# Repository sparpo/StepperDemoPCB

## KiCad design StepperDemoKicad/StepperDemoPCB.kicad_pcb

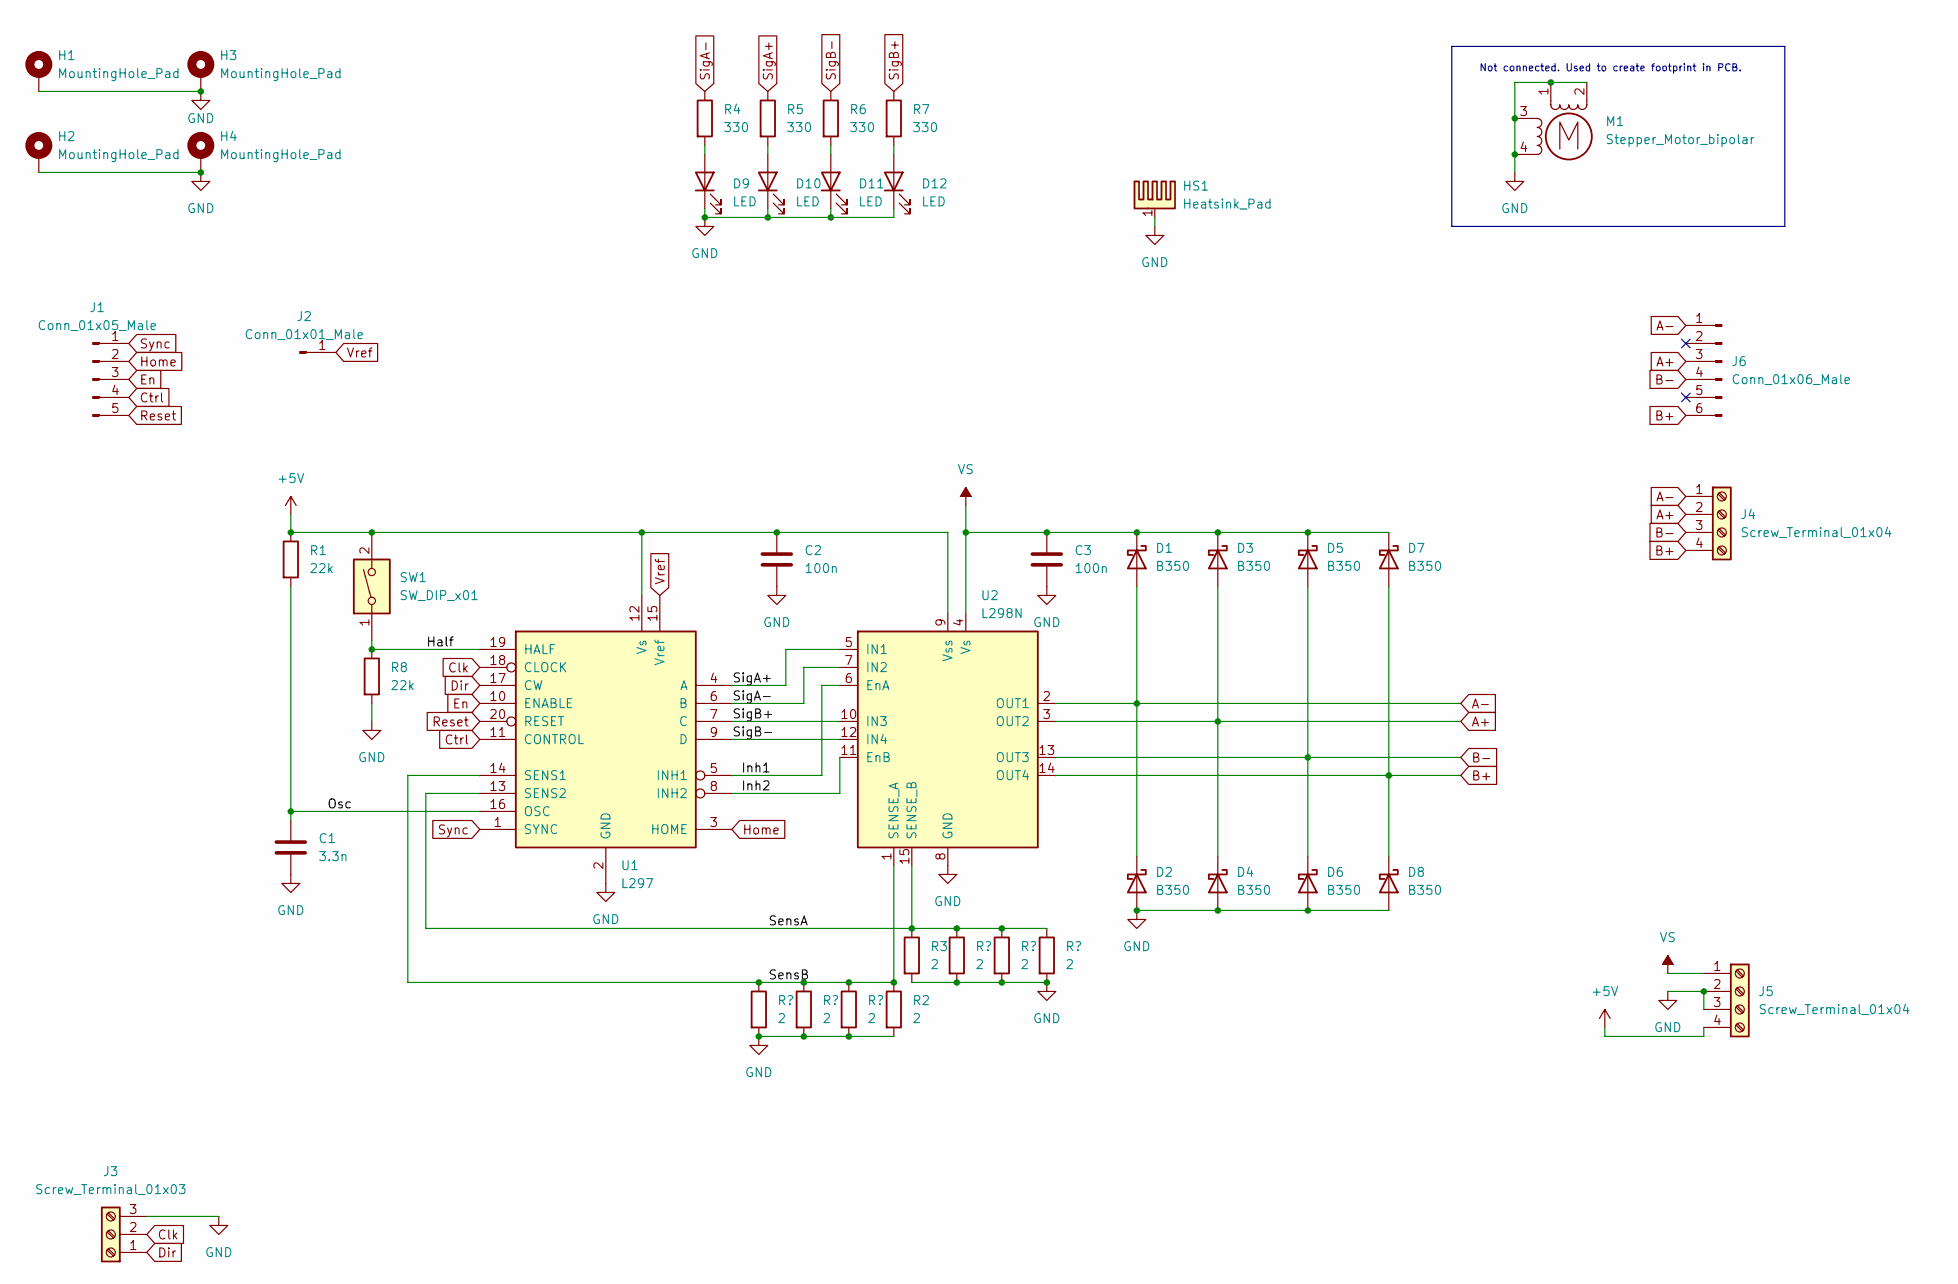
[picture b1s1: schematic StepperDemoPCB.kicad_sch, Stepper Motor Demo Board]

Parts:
C1: 3.3n; C_0805_2012Metric_Pad1.18x1.45mm_HandSolder
C2, C3: 100n; C_0805_2012Metric_Pad1.18x1.45mm_HandSolder
D1, D2, D3, D4, D5, D6, D7, D8: B350; D_SMC
D9, D10, D11, D12: LED; LED_D5.0mm
H1, H2, H3, H4: MountingHole_Pad; MountingHole_4.3mm_M4_DIN965_Pad
HS1: Heatsink_Pad; 42x25mm_multiwatt15
J1: Conn_01x05_Male; PinSocket_1x05_P2.54mm_Vertical
J2: Conn_01x01_Male; PinSocket_1x01_P2.54mm_Vertical
J3: Screw_Terminal_01x03; TerminalBlock_bornier-3_P5.08mm
J4, J5: Screw_Terminal_01x04; TerminalBlock_bornier-4_P5.08mm
J6: Conn_01x06_Male; PinHeader_1x06_P2.54mm_Vertical
M1: Stepper_Motor_bipolar; nema17
R1, R8: 22k; R_0805_2012Metric_Pad1.20x1.40mm_HandSolder
R2, R3: 2; R_2512_6332Metric_Pad1.40x3.35mm_HandSolder
R4, R5, R6, R7: 330; R_0805_2012Metric_Pad1.20x1.40mm_HandSolder
SW1: SW_DIP_x01; SW_DIP_SPSTx01_Slide_6.7x4.1mm_W7.62mm_P2.54mm_LowProfile
U1: L297; DIP-20_W7.62mm
U2: L298N; TO-220-15_P2.54x2.54mm_StaggerOdd_Lead4.58mm_Vertical

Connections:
+5V: C2.1, J5.4, R1.1, SW1.2, U1.12 (Vs), U2.9 (Vss)
/Half: R8.1, SW1.1, U1.19 (HALF)
/Inh1: U1.5 (INH1), U2.6 (EnA)
/Inh2: U1.8 (INH2), U2.11 (EnB)
/Osc: C1.1, R1.2, U1.16 (OSC)
/SensA: R3.1, U1.13 (SENS2), U2.15 (SENSE_B)
/SensB: R2.1, U1.14 (SENS1), U2.1 (SENSE_A)
A+: D3.2 (A), D4.1 (K), J4.2, J6.3, U2.3 (OUT2)
A-: D1.2 (A), D2.1 (K), J4.1, J6.1, U2.2 (OUT1)
B+: D7.2 (A), D8.1 (K), J4.4, J6.6, U2.14 (OUT4)
B-: D5.2 (A), D6.1 (K), J4.3, J6.4, U2.13 (OUT3)
Clk: J3.2, U1.18 (CLOCK)
Ctrl: J1.4, U1.11 (CONTROL)
Dir: J3.1, U1.17 (CW)
En: J1.3, U1.10 (ENABLE)
GND: C1.2, C2.2, C3.2, D2.2 (A), D4.2 (A), D6.2 (A), D8.2 (A), D9.1 (K), D10.1 (K), D11.1 (K), D12.1 (K), H1.1, H2.1, H3.1, H4.1, HS1.1, J3.3, J5.2, J5.3, M1.1, M1.2 (-), M1.3, M1.4, R2.2, R3.2, R8.2, U1.2 (GND), U2.8 (GND)
Home: J1.2, U1.3 (HOME)
unnamed: D9.2 (A), R4.2
unnamed: D10.2 (A), R5.2
unnamed: D11.2 (A), R6.2
unnamed: D12.2 (A), R7.2
Reset: J1.5, U1.20 (RESET)
SigA+: R5.1, U1.4 (A), U2.5 (IN1)
SigA-: R4.1, U1.6 (B), U2.7 (IN2)
SigB+: R7.1, U1.7 (C), U2.10 (IN3)
SigB-: R6.1, U1.9 (D), U2.12 (IN4)
Sync: J1.1, U1.1 (SYNC)
VS: C3.1, D1.1 (K), D3.1 (K), D5.1 (K), D7.1 (K), J5.1, U2.4 (Vs)
Vref: J2.1, U1.15 (Vref)

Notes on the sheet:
Not connected. Used to create footprint in PCB.

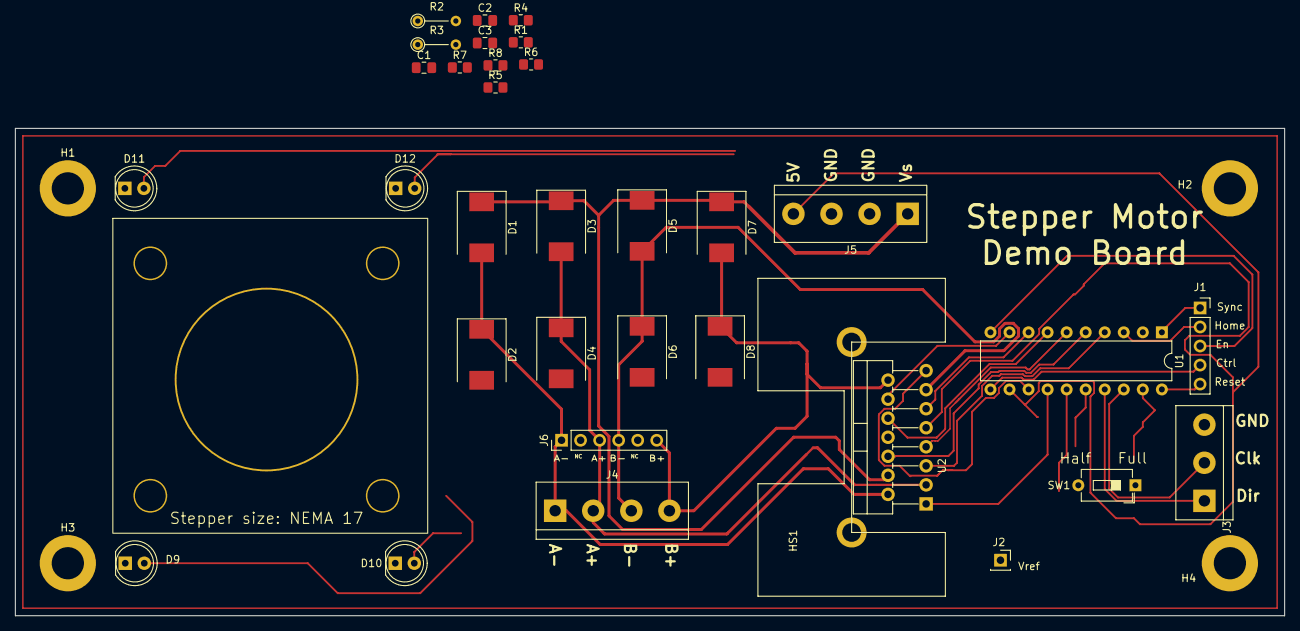
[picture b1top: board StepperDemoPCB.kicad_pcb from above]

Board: 2 copper layers, 169.3 x 65.0 mm, 38 parts (0 on the bottom side), 29 nets.

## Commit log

2023-02-11 Files
    added all current project files
2023-02-11 smd Diode
2023-02-12 Added heatsink
2023-02-12 SMD resistors
